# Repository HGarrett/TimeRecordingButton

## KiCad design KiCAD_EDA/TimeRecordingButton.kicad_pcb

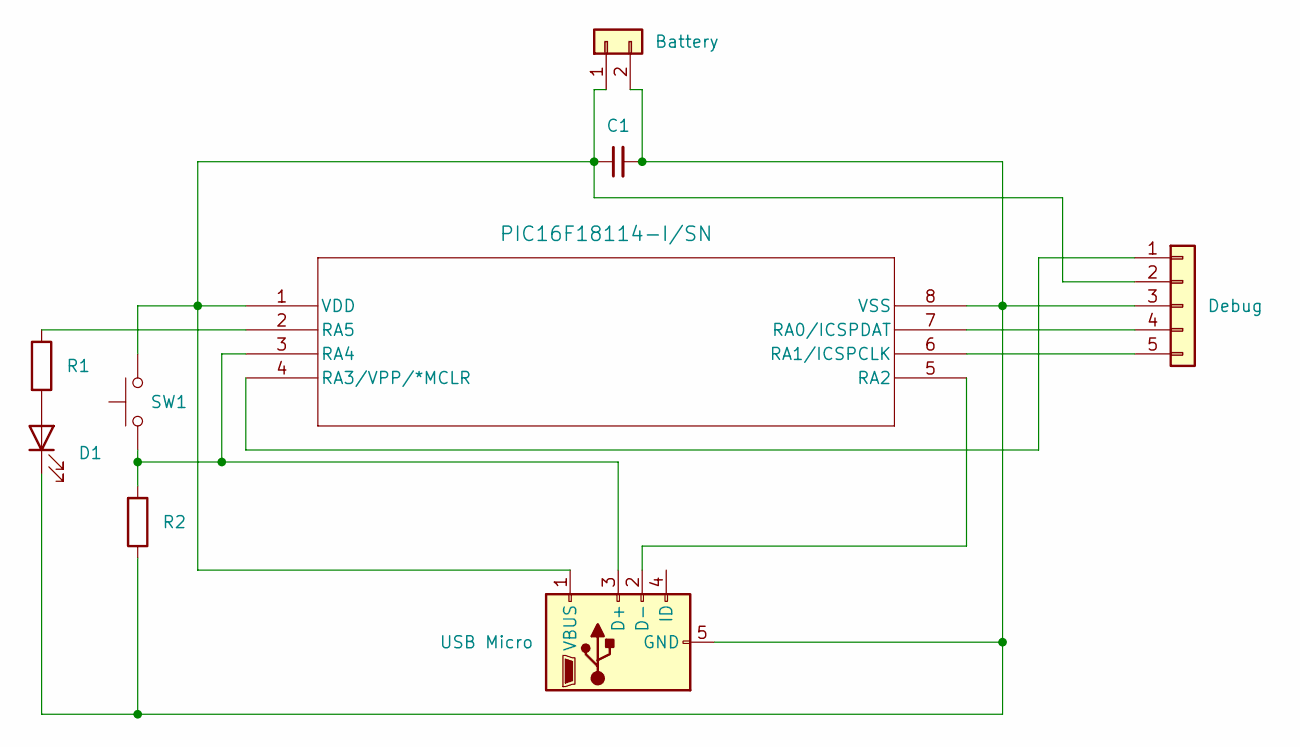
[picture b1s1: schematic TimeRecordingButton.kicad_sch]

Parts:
C1: C_Small; C_0603_1608Metric_Pad1.08x0.95mm_HandSolder
D1: LED; D_1206_3216Metric_Pad1.42x1.75mm_HandSolder
J1: USB Micro; USB_Micro-B_Custom1
J2: Battery; JST_PH_B2B-PH-SM4-TB_1x02-1MP_P2.00mm_Vertical
J3: Debug; PinSocket_1x05_P2.54mm_Vertical
R1, R2: R; R_1206_3216Metric_Pad1.30x1.75mm_HandSolder
SW1: SW_Push; TouchButton-5x5mm
U2: PIC16F18114-I/SN; SOIC8_SN_MCH

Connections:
unnamed: D1.2 (A), R1.2
unnamed: C1.2, D1.1 (K), J1.5 (GND), J2.2, J3.3, R2.1, U2.8 (VSS)
unnamed: J1.3 (D+), R2.2, SW1.2, U2.3 (RA4)
unnamed: J1.2 (D-), U2.5 (RA2)
unnamed: C1.1, J1.1 (VBUS), J2.1, J3.2, SW1.1, U2.1 (VDD)
unnamed: J3.1, U2.4 (RA3/VPP/*MCLR)
unnamed: J3.4, U2.7 (RA0/ICSPDAT)
unnamed: J3.5, U2.6 (RA1/ICSPCLK)
unnamed: R1.1, U2.2 (RA5)

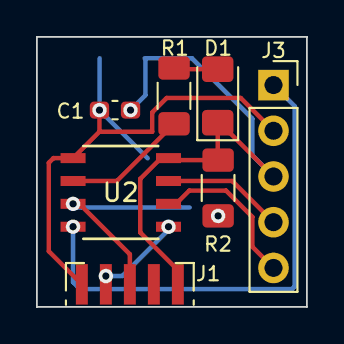
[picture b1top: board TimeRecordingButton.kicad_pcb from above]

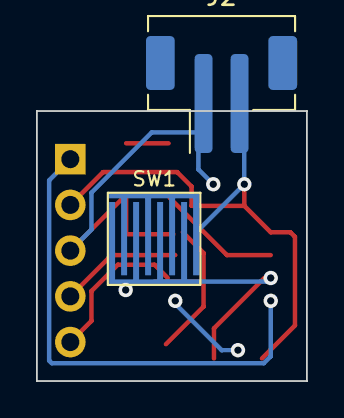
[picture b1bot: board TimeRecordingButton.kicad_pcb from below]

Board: 2 copper layers, 15.0 x 15.0 mm, 9 parts (2 on the bottom side), 9 nets.

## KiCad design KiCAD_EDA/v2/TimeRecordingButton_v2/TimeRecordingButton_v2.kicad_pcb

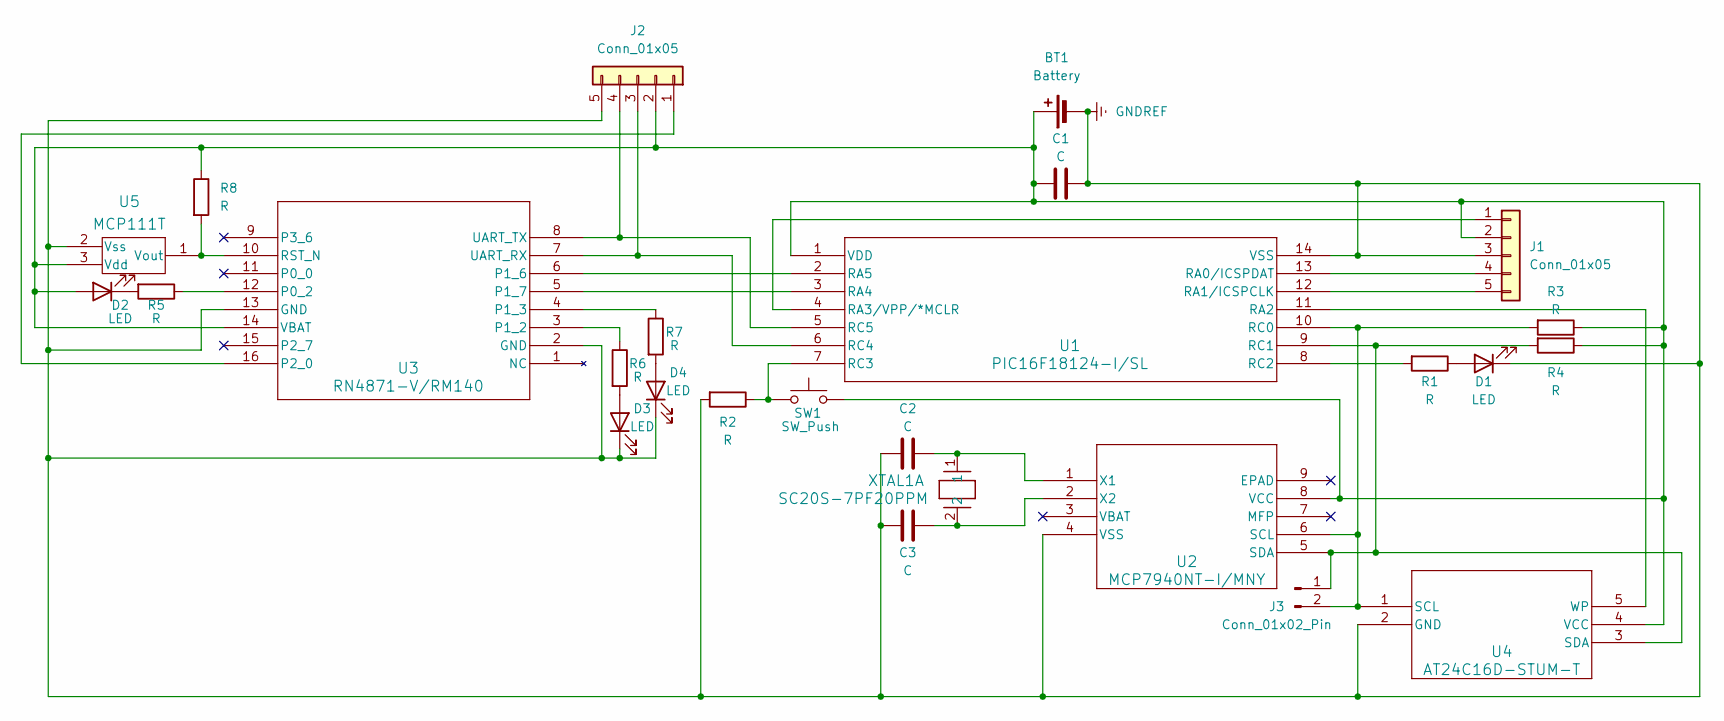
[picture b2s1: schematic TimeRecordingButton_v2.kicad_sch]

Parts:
BT1: Battery; Adafruit_JST_PH_2_Pin_SMT
C1, C2, C3: C; C_0603_1608Metric_Pad1.08x0.95mm_HandSolder
D1: LED; D_1206_3216Metric_Pad1.42x1.75mm_HandSolder
D2, D3, D4: LED; LED_LTST-C191KRKT_LTO-L
J1, J2: Conn_01x05; TestPoint_1x05_P1.00mm
J3: Conn_01x02_Pin; TestPoint_1x02_P1.00mm
R1, R2, R3, R4, R5, R6, R7, R8: R; R_0603_1608Metric_Pad0.98x0.95mm_HandSolder
SW1: SW_Push; TouchButton-5x5mm
U1: PIC16F18124-I/SL; PIC16F18124_I_SL
U2: MCP7940NT-I/MNY; TDFN8_2x3MC_MCH
U3: RN4871-V/RM140; RN4871_MCH
U4: AT24C16D-STUM-T; TSOT5_MC_MCH
U5: MCP111T; SC70-3_MC_MCH
XTAL1: SC20S-7PF20PPM; XTAL_SC-20S_EPS

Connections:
GNDREF: BT1.2 (-), C1.2, C2.1, C3.1, D1.1 (K), D3.1 (K), D4.1 (K), J1.3, J2.5, R2.2, U1.14 (VSS), U2.4 (VSS), U3.2 (GND), U3.13 (GND), U4.2 (GND), U5.2 (Vss)
unnamed: BT1.1 (+), C1.1, D2.2 (A), J1.2, J2.2, R3.1, R4.1, R8.1, SW1.2, U1.1 (VDD), U2.8 (VCC), U3.14 (VBAT), U4.4 (VCC), U5.3 (Vdd)
unnamed: D1.2 (A), R1.1
unnamed: D2.1 (K), R5.2
unnamed: D3.2 (A), R6.2
unnamed: D4.2 (A), R7.2
unnamed: J1.1, U1.4 (RA3/VPP/*MCLR)
unnamed: J1.4, U1.13 (RA0/ICSPDAT)
unnamed: J1.5, U1.12 (RA1/ICSPCLK)
unnamed: J2.1, U3.16 (P2_0)
unnamed: J2.3, U1.6 (RC4), U3.7 (UART_RX)
unnamed: J2.4, U1.5 (RC5), U3.8 (UART_TX)
unnamed: J3.1, R4.2, U1.9 (RC1), U2.5 (SDA), U4.3 (SDA)
unnamed: J3.2, R3.2, U1.10 (RC0), U2.6 (SCL), U4.1 (SCL)
unnamed: U1.11 (RA2), U4.5 (WP)
unnamed: U1.3 (RA4), U3.5 (P1_7)
unnamed: U1.2 (RA5), U3.6 (P1_6)
unnamed: R1.2, U1.8 (RC2)
unnamed: R2.1, SW1.1, U1.7 (RC3)
unnamed: C2.2, U2.1 (X1), XTAL1.1
unnamed: C3.2, U2.2 (X2), XTAL1.2
unnamed: R5.1, U3.12 (P0_2)
unnamed: R6.1, U3.3 (P1_2)
unnamed: R7.1, U3.4 (P1_3)
unnamed: R8.2, U3.10 (RST_N), U5.1 (Vout)

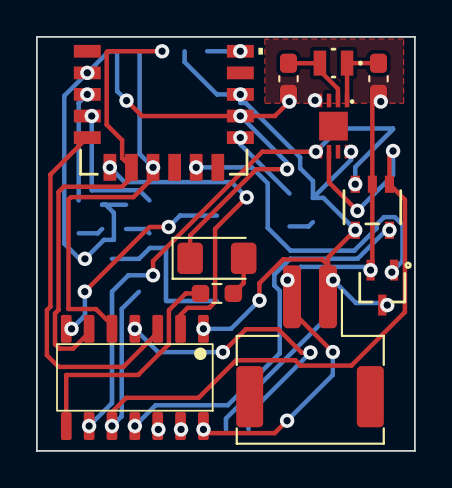
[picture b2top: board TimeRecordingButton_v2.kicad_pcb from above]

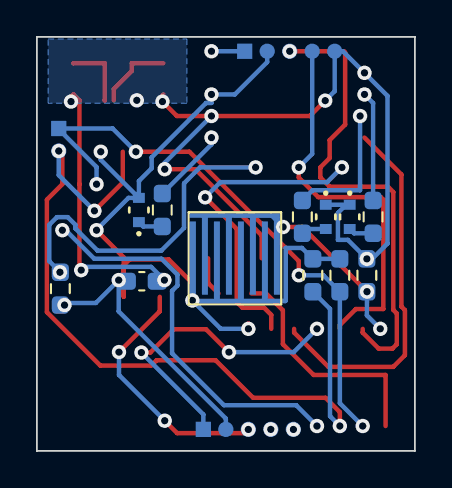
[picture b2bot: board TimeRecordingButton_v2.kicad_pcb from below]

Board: 2 copper layers, 21.0 x 23.0 mm, 26 parts (15 on the bottom side), 25 nets.

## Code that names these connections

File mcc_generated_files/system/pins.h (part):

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// get/set IO_RA2 aliases
#define EEPROM_WP_TRIS                 TRISAbits.TRISA2
#define EEPROM_WP_LAT                  LATAbits.LATA2
#define EEPROM_WP_PORT                 PORTAbits.RA2
#define EEPROM_WP_WPU                  WPUAbits.WPUA2
#define EEPROM_WP_OD                   ODCONAbits.ODCA2
#define EEPROM_WP_ANS                  ANSELAbits.ANSA2
#define EEPROM_WP_SetHigh()            do { LATAbits.LATA2 = 1; } while(0)
#define EEPROM_WP_SetLow()             do { LATAbits.LATA2 = 0; } while(0)
#define EEPROM_WP_Toggle()             do { LATAbits.LATA2 = ~LATAbits.LATA2; } while(0)
#define EEPROM_WP_GetValue()           PORTAbits.RA2
#define EEPROM_WP_SetDigitalInput()    do { TRISAbits.TRISA2 = 1; } while(0)
#define EEPROM_WP_SetDigitalOutput()   do { TRISAbits.TRISA2 = 0; } while(0)
#define EEPROM_WP_SetPullup()          do { WPUAbits.WPUA2 = 1; } while(0)
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// get/set IO_RA4 aliases
#define RN4871_LowBat_TRIS                 TRISAbits.TRISA4
#define RN4871_LowBat_LAT                  LATAbits.LATA4
#define RN4871_LowBat_PORT                 PORTAbits.RA4
#define RN4871_LowBat_WPU                  WPUAbits.WPUA4
#define RN4871_LowBat_OD                   ODCONAbits.ODCA4
#define RN4871_LowBat_ANS                  ANSELAbits.ANSA4
#define RN4871_LowBat_SetHigh()            do { LATAbits.LATA4 = 1; } while(0)
#define RN4871_LowBat_SetLow()             do { LATAbits.LATA4 = 0; } while(0)
#define RN4871_LowBat_Toggle()             do { LATAbits.LATA4 = ~LATAbits.LATA4; } while(0)
#define RN4871_LowBat_GetValue()           PORTAbits.RA4
#define RN4871_LowBat_SetDigitalInput()    do { TRISAbits.TRISA4 = 1; } while(0)
#define RN4871_LowBat_SetDigitalOutput()   do { TRISAbits.TRISA4 = 0; } while(0)
#define RN4871_LowBat_SetPullup()          do { WPUAbits.WPUA4 = 1; } while(0)
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// get/set IO_RA5 aliases
#define RN4871_RX_Ind_TRIS                 TRISAbits.TRISA5
#define RN4871_RX_Ind_LAT                  LATAbits.LATA5
#define RN4871_RX_Ind_PORT                 PORTAbits.RA5
#define RN4871_RX_Ind_WPU                  WPUAbits.WPUA5
#define RN4871_RX_Ind_OD                   ODCONAbits.ODCA5
#define RN4871_RX_Ind_ANS                  ANSELAbits.ANSA5
#define RN4871_RX_Ind_SetHigh()            do { LATAbits.LATA5 = 1; } while(0)
#define RN4871_RX_Ind_SetLow()             do { LATAbits.LATA5 = 0; } while(0)
#define RN4871_RX_Ind_Toggle()             do { LATAbits.LATA5 = ~LATAbits.LATA5; } while(0)
#define RN4871_RX_Ind_GetValue()           PORTAbits.RA5
#define RN4871_RX_Ind_SetDigitalInput()    do { TRISAbits.TRISA5 = 1; } while(0)
#define RN4871_RX_Ind_SetDigitalOutput()   do { TRISAbits.TRISA5 = 0; } while(0)
#define RN4871_RX_Ind_SetPullup()          do { WPUAbits.WPUA5 = 1; } while(0)
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// get/set IO_RC0 aliases
#define EEPROM_RTCC_CLK_TRIS                 TRISCbits.TRISC0
#define EEPROM_RTCC_CLK_LAT                  LATCbits.LATC0
#define EEPROM_RTCC_CLK_PORT                 PORTCbits.RC0
#define EEPROM_RTCC_CLK_WPU                  WPUCbits.WPUC0
#define EEPROM_RTCC_CLK_OD                   ODCONCbits.ODCC0
#define EEPROM_RTCC_CLK_ANS                  ANSELCbits.ANSC0
#define EEPROM_RTCC_CLK_SetHigh()            do { LATCbits.LATC0 = 1; } while(0)
#define EEPROM_RTCC_CLK_SetLow()             do { LATCbits.LATC0 = 0; } while(0)
#define EEPROM_RTCC_CLK_Toggle()             do { LATCbits.LATC0 = ~LATCbits.LATC0; } while(0)
#define EEPROM_RTCC_CLK_GetValue()           PORTCbits.RC0
#define EEPROM_RTCC_CLK_SetDigitalInput()    do { TRISCbits.TRISC0 = 1; } while(0)
#define EEPROM_RTCC_CLK_SetDigitalOutput()   do { TRISCbits.TRISC0 = 0; } while(0)
#define EEPROM_RTCC_CLK_SetPullup()          do { WPUCbits.WPUC0 = 1; } while(0)
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// get/set IO_RC1 aliases
#define EEPROM_RTCC_DAT_TRIS                 TRISCbits.TRISC1
#define EEPROM_RTCC_DAT_LAT                  LATCbits.LATC1
#define EEPROM_RTCC_DAT_PORT                 PORTCbits.RC1
#define EEPROM_RTCC_DAT_WPU                  WPUCbits.WPUC1
#define EEPROM_RTCC_DAT_OD                   ODCONCbits.ODCC1
#define EEPROM_RTCC_DAT_ANS                  ANSELCbits.ANSC1
#define EEPROM_RTCC_DAT_SetHigh()            do { LATCbits.LATC1 = 1; } while(0)
#define EEPROM_RTCC_DAT_SetLow()             do { LATCbits.LATC1 = 0; } while(0)
#define EEPROM_RTCC_DAT_Toggle()             do { LATCbits.LATC1 = ~LATCbits.LATC1; } while(0)
#define EEPROM_RTCC_DAT_GetValue()           PORTCbits.RC1
#define EEPROM_RTCC_DAT_SetDigitalInput()    do { TRISCbits.TRISC1 = 1; } while(0)
#define EEPROM_RTCC_DAT_SetDigitalOutput()   do { TRISCbits.TRISC1 = 0; } while(0)
#define EEPROM_RTCC_DAT_SetPullup()          do { WPUCbits.WPUC1 = 1; } while(0)
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// get/set IO_RC2 aliases
#define Switch_LED_TRIS                 TRISCbits.TRISC2
#define Switch_LED_LAT                  LATCbits.LATC2
#define Switch_LED_PORT                 PORTCbits.RC2
#define Switch_LED_WPU                  WPUCbits.WPUC2
#define Switch_LED_OD                   ODCONCbits.ODCC2
#define Switch_LED_ANS                  ANSELCbits.ANSC2
#define Switch_LED_SetHigh()            do { LATCbits.LATC2 = 1; } while(0)
#define Switch_LED_SetLow()             do { LATCbits.LATC2 = 0; } while(0)
#define Switch_LED_Toggle()             do { LATCbits.LATC2 = ~LATCbits.LATC2; } while(0)
#define Switch_LED_GetValue()           PORTCbits.RC2
#define Switch_LED_SetDigitalInput()    do { TRISCbits.TRISC2 = 1; } while(0)
#define Switch_LED_SetDigitalOutput()   do { TRISCbits.TRISC2 = 0; } while(0)
#define Switch_LED_SetPullup()          do { WPUCbits.WPUC2 = 1; } while(0)
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// get/set IO_RC3 aliases
#define Switch_TRIS                 TRISCbits.TRISC3
#define Switch_LAT                  LATCbits.LATC3
#define Switch_PORT                 PORTCbits.RC3
#define Switch_WPU                  WPUCbits.WPUC3
#define Switch_OD                   ODCONCbits.ODCC3
#define Switch_ANS                  ANSELCbits.ANSC3
#define Switch_SetHigh()            do { LATCbits.LATC3 = 1; } while(0)
#define Switch_SetLow()             do { LATCbits.LATC3 = 0; } while(0)
#define Switch_Toggle()             do { LATCbits.LATC3 = ~LATCbits.LATC3; } while(0)
#define Switch_GetValue()           PORTCbits.RC3
#define Switch_SetDigitalInput()    do { TRISCbits.TRISC3 = 1; } while(0)
#define Switch_SetDigitalOutput()   do { TRISCbits.TRISC3 = 0; } while(0)
#define Switch_SetPullup()          do { WPUCbits.WPUC3 = 1; } while(0)
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// get/set IO_RC4 aliases
#define RN4871_TX_TRIS                 TRISCbits.TRISC4
#define RN4871_TX_LAT                  LATCbits.LATC4
#define RN4871_TX_PORT                 PORTCbits.RC4
#define RN4871_TX_WPU                  WPUCbits.WPUC4
#define RN4871_TX_OD                   ODCONCbits.ODCC4
#define RN4871_TX_ANS                  ANSELCbits.ANSC4
#define RN4871_TX_SetHigh()            do { LATCbits.LATC4 = 1; } while(0)
#define RN4871_TX_SetLow()             do { LATCbits.LATC4 = 0; } while(0)
#define RN4871_TX_Toggle()             do { LATCbits.LATC4 = ~LATCbits.LATC4; } while(0)
#define RN4871_TX_GetValue()           PORTCbits.RC4
#define RN4871_TX_SetDigitalInput()    do { TRISCbits.TRISC4 = 1; } while(0)
#define RN4871_TX_SetDigitalOutput()   do { TRISCbits.TRISC4 = 0; } while(0)
#define RN4871_TX_SetPullup()          do { WPUCbits.WPUC4 = 1; } while(0)
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// get/set IO_RC5 aliases
#define RN4871_RX_TRIS                 TRISCbits.TRISC5
#define RN4871_RX_LAT                  LATCbits.LATC5
#define RN4871_RX_PORT                 PORTCbits.RC5
#define RN4871_RX_WPU                  WPUCbits.WPUC5
#define RN4871_RX_OD                   ODCONCbits.ODCC5
#define RN4871_RX_ANS                  ANSELCbits.ANSC5
#define RN4871_RX_SetHigh()            do { LATCbits.LATC5 = 1; } while(0)
#define RN4871_RX_SetLow()             do { LATCbits.LATC5 = 0; } while(0)
#define RN4871_RX_Toggle()             do { LATCbits.LATC5 = ~LATCbits.LATC5; } while(0)
#define RN4871_RX_GetValue()           PORTCbits.RC5
#define RN4871_RX_SetDigitalInput()    do { TRISCbits.TRISC5 = 1; } while(0)
#define RN4871_RX_SetDigitalOutput()   do { TRISCbits.TRISC5 = 0; } while(0)
#define RN4871_RX_SetPullup()          do { WPUCbits.WPUC5 = 1; } while(0)
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
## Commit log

2023-10-16 Removing build code
2023-10-16 Updating gitignore to ignore build folders
2023-10-17 Major update which inclues chip update, use with caution
2023-10-26 Updates for fixed bugs with actual hardware. LED timing still needs work.
2023-11-13 Added KiCAD project files and Gerber files submitted today to JLCPCB
2023-11-17 Added UART code and fixed a few bugs.
2023-11-18 Fixed timer code. Needed to read L before H and fix prescaler and postscaler for proper timer ticks.
2023-12-26 KiCAD v2 and removing backup folders.
2024-02-08 TEMP: Old work needs revamp for version 2
2024-02-11 Retired old code and used generated code by MPLab. See what happens.
2024-02-12 Added the sudo cli for sending cmd bindings through UART. Everything compiles and runs on the PIC16. Nothing is really tested past that.
2024-02-12 Changed clock speed to support the new set baudrate of 115200.
2024-02-12 Cleanup and changes to get ready to communicate with RN4870 for init before cli enable. Builds, but no other testing.
2024-02-25 Changing chip to bigger memory version and finishing up GPIO pins in MCC.
2024-02-26 Removing a private file that didn't get removed properly before.
